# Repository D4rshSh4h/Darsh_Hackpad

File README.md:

# Darsh_Hackpad
A 6-Key macropad designed to carry out common shortcuts quickly.

## Features:
- 3D printed case and cover
- 6x cherry-mx style keys
- 1x EC11 Rotary encoder
- 1x SK6812 MINI LEDs
- 1x Seeed XIAD RP2040

## Case:
The case and cover, both designed in Fusion360

## Schematic and PCB:
Screenshots of both schematics and PCB design, done on KiCAD

## Overall Look:
Screenshots of the overall hackpad with 3D models of keys and the rotary encoder to provide further detail

## With 3D model of PCB

Thanks!!

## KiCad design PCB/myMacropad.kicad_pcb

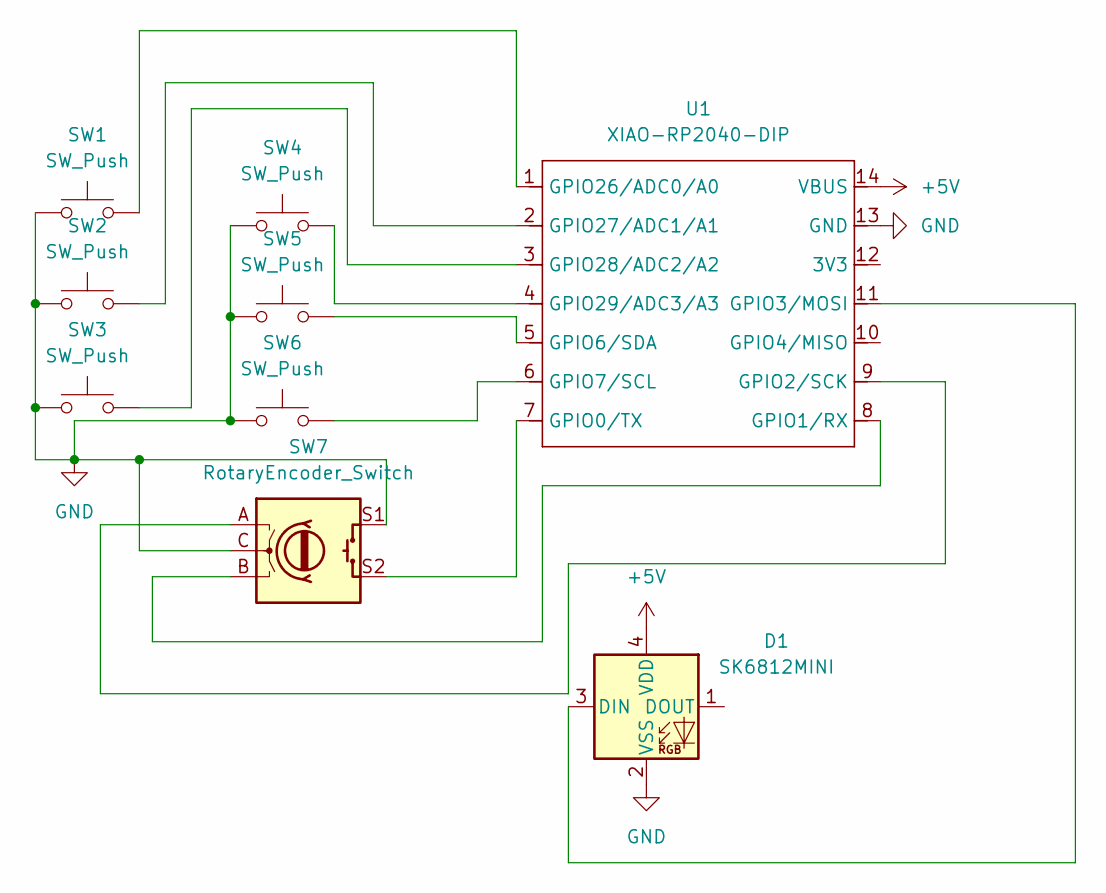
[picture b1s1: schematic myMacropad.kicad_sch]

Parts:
D1: SK6812MINI; LED_SK6812MINI_PLCC4_3.5x3.5mm_P1.75mm
SW1, SW2, SW3, SW4, SW5, SW6: SW_Push; SW_Cherry_MX_1.00u_PCB
SW7: RotaryEncoder_Switch; RotaryEncoder_Alps_EC11E-Switch_Vertical_H20mm
U1: XIAO-RP2040-DIP

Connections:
+5V: D1.4 (VDD), U1.14 (VBUS)
GND: D1.2 (VSS), SW1.1, SW2.1, SW3.1, SW4.1, SW5.1, SW6.1, SW7.C, SW7.S1, U1.13 (GND)
unnamed: D1.3 (DIN), U1.11 (GPIO3/MOSI)
unnamed: SW7.S2, U1.7 (GPIO0/TX)
unnamed: SW7.B, U1.8 (GPIO1/RX)
unnamed: SW7.A, U1.9 (GPIO2/SCK)
unnamed: SW5.2, U1.5 (GPIO6/SDA)
unnamed: SW6.2, U1.6 (GPIO7/SCL)
unnamed: SW1.2, U1.1 (GPIO26/ADC0/A0)
unnamed: SW2.2, U1.2 (GPIO27/ADC1/A1)
unnamed: SW3.2, U1.3 (GPIO28/ADC2/A2)
unnamed: SW4.2, U1.4 (GPIO29/ADC3/A3)

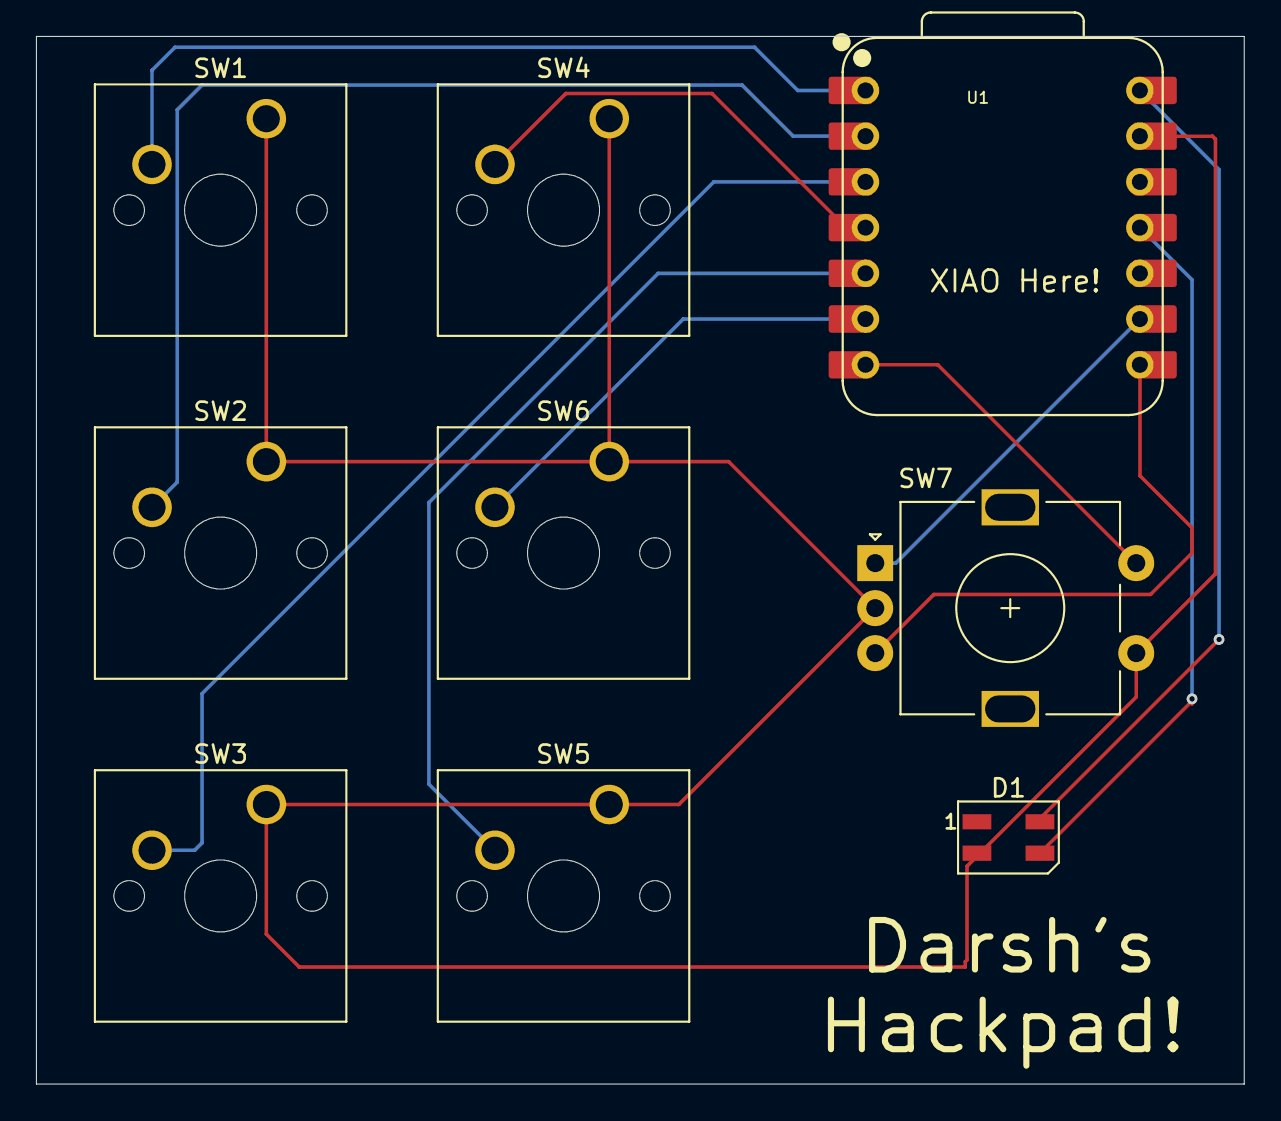
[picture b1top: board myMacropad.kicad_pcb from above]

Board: 2 copper layers, 67.1 x 58.2 mm, 9 parts (0 on the bottom side), 12 nets.

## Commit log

2025-12-13 Enhance README with detailed project information
    Added detailed features, case information, schematic, PCB, and overall look sections.
2025-12-13 added files
2025-12-16 firmaware commited
2025-12-16 updated firmaware
2025-12-25 Add 3D model section to README
    Added section for 3D model of PCB with images.
2025-12-25 Add new image to README for PCB model
